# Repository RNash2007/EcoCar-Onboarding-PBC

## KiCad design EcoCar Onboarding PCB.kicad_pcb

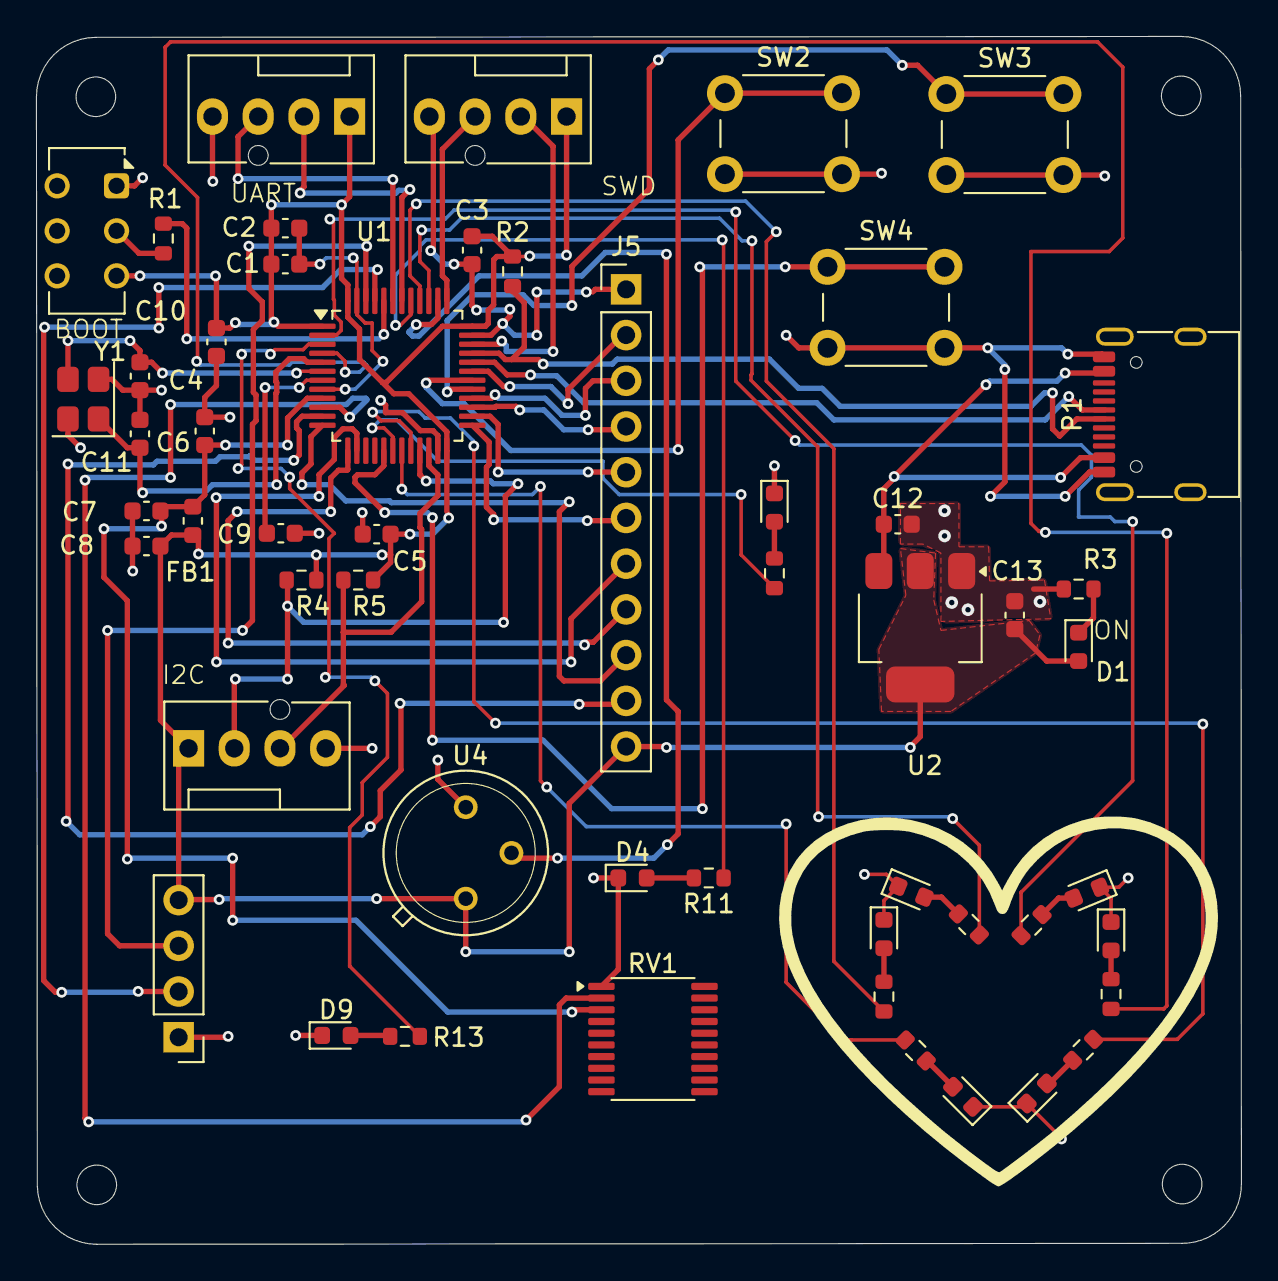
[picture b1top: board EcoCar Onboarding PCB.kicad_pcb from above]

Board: 2 copper layers, 66.9 x 67.1 mm, 57 parts (0 on the bottom side), 52 nets.

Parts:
C1, C2, C3, C4, C9: 100n; C_0603_1608Metric
C5: 10u; C_0603_1608Metric
C6: 10n; C_0603_1608Metric
C7, C8: 1u; C_0603_1608Metric
C10, C11: 10p; C_0603_1608Metric
C12, C13: 22u; C_0603_1608Metric
D1, D9: RED; LED_0603_1608Metric
D2, D3, D5, D6, D8, D10: PINK; LED_0603_1608Metric
D4: GREEN; LED_0603_1608Metric
D7: BLUE; LED_0603_1608Metric
FB1: 120R; L_0603_1608Metric
H1, H2, H3, H4: MountingHole; MountingHole_2.2mm_M2
J1: Conn_01x04_Pin; PinHeader_1x04_P2.54mm_Vertical
J2, J3, J4: Conn_01x04_Pin; FanPinHeader_1x04_P2.54mm_Vertical
J5: Conn_01x11_Pin; PinHeader_1x11_P2.54mm_Vertical
P1: USB_C_Plug_USB2.0; USB_C_Receptacle_G-Switch_GT-USB-7010ASV
R1: 10k; R_0603_1608Metric
R2, R3, R4, R5, R6, R7, R8, R9, R10, R11, R12, R13, R14: 1k5; R_0603_1608Metric
RV1: R_Potentiometer; TSSOP-20_4.4x6.5mm_P0.65mm
SW1: SW_SPDT; SW_CK_JS202011CQN_DPDT_Straight
SW2, SW3, SW4: SW_Push; SW_PUSH_6mm_H5mm
U1: STM32F103C8T6; LQFP-48_7x7mm_P0.5mm
U2: AMS1117-3.3; SOT-223-3_TabPin2
U4: ZRE200GE; TO5
Y1: 16MHz; Crystal_SMD_3225-4Pin_3.2x2.5mm

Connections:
+3.3V: C1.1, C2.1, C3.1, C4.1, C5.1, C8.1, C13.1, D1.2 (A), FB1.1, J1.4, J2.1, J3.1, J4.1, J5.11, R2.1, R4.1, R5.1, SW1.3 (C), U1.1 (VBAT), U1.24 (VDD), U1.36 (VDD), U1.48 (VDD), U2.2 (VO), U4.1
+3.3VA: C6.1, C7.1, FB1.2, RV1.3, U1.9 (VDDA)
/BOOT0: R1.2, U1.44 (BOOT0)
/HSE_IN: C11.1, U1.5 (PD0), Y1.1
/HSE_OUT: C10.1, U1.6 (PD1), Y1.3
/I2C2_SCL: J4.2, R4.2, U1.21 (PB10)
/I2C2_SDA: J4.3, R5.2, U1.22 (PB11)
/LED1: R6.1, U1.19 (PB1)
/LED2: R7.1, U1.20 (PB2)
/LED3: R9.1, U1.39 (PB3)
/LED4: R10.1, U1.40 (PB4)
/LED5: R11.1, U1.41 (PB5)
/LED6: R12.1, U1.4 (PC15)
/LED7: R13.1, U1.3 (PC14)
/LED8: R14.1, U1.2 (PC13)
/NRST: C9.1, U1.7 (NRST)
/P1: J5.2, U1.31 (PA10)
/P2: J5.3, U1.28 (PB15)
/P3: J5.4, U1.27 (PB14)
/P4: J5.5, U1.26 (PB13)
/P5: J5.6, U1.25 (PB12)
/P6: J5.7, U1.14 (PA4)
/P7: J5.8, U1.13 (PA3)
/P8: J5.9, U1.12 (PA2)
/P9: J5.10, U1.11 (PA1)
/PWR_LED_K: D1.1 (K), R3.1
/Pins for screen: J1.3, U1.46 (PB9)
/SWCLK: J2.3, U1.37 (PA14)
/SWDIO: J2.2, U1.34 (PA13)
/SW_BOOT0: R1.1, SW1.2 (B)
/TIMER_LED: R8.1, U1.18 (PB0)
/USART1_RX: J3.3, U1.43 (PB7)
/USART1_TX: J3.2, U1.42 (PB6)
/USB_D+: P1.A6 (D+), R2.2, U1.33 (PA12)
/USB_D-: P1.A7 (D-), U1.32 (PA11)
GND: C1.2, C2.2, C3.2, C4.2, C5.2, C6.2, C7.2, C8.2, C9.2, C10.2, C11.2, C12.2, C13.2, D2.1 (K), D3.1 (K), D4.1 (K), D5.1 (K), D6.1 (K), D7.1 (K), D8.1 (K), D9.1 (K), D10.1 (K), J1.1, J2.4, J3.4, J4.4, J5.1, P1.A1 (GND), P1.A12 (GND), P1.B1 (GND), P1.B12 (GND), R3.2, RV1.1, SW1.1 (A), SW2.2, SW3.2, SW4.2, U1.8 (VSSA), U1.23 (VSS), U1.35 (VSS), U1.47 (VSS), U2.1 (GND), U4.3, Y1.2 (G), Y1.4 (G)
unnamed: D2.2 (A), R10.2
unnamed: D3.2 (A), R6.2
unnamed: D4.2 (A), R11.2
unnamed: D5.2 (A), R12.2
unnamed: D6.2 (A), R7.2
unnamed: D7.2 (A), R8.2
unnamed: D8.2 (A), R9.2
unnamed: D9.2 (A), R13.2
unnamed: D10.2 (A), R14.2
unnamed: J1.2, U1.45 (PB8)
unnamed: RV1.2, U1.10 (PA0)
unnamed: SW4.1, U1.17 (PA7)
unnamed: SW3.1, U1.29 (PA8)
unnamed: SW2.1, U1.30 (PA9)
unnamed: U1.38 (PA15), U4.2
VBUS: C12.1, P1.A4 (VBUS), P1.A9 (VBUS), P1.B4 (VBUS), P1.B9 (VBUS), U2.3 (VI)

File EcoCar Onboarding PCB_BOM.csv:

"Reference","Qty","Value","DNP","Exclude from BOM","Exclude from Board","Exclude from Simulation","Exclude from Position Files","Footprint","Datasheet"
"C1,C2,C3,C4,C9","5","100n","","","","","${EXCLUDE_FROM_POS_FILES}","Capacitor_SMD:C_0603_1608Metric",""
"C5","1","10u","","","","","${EXCLUDE_FROM_POS_FILES}","Capacitor_SMD:C_0603_1608Metric",""
"C6","1","10n","","","","","${EXCLUDE_FROM_POS_FILES}","Capacitor_SMD:C_0603_1608Metric",""
"C7,C8","2","1u","","","","","${EXCLUDE_FROM_POS_FILES}","Capacitor_SMD:C_0603_1608Metric",""
"C10,C11","2","10p","","","","","${EXCLUDE_FROM_POS_FILES}","Capacitor_SMD:C_0603_1608Metric",""
"C12,C13","2","22u","","","","","${EXCLUDE_FROM_POS_FILES}","Capacitor_SMD:C_0603_1608Metric",""
"D1,D9","2","RED","","","","","${EXCLUDE_FROM_POS_FILES}","LED_SMD:LED_0603_1608Metric",""
"D2,D3,D5,D6,D8,D10","6","PINK","","","","","${EXCLUDE_FROM_POS_FILES}","LED_SMD:LED_0603_1608Metric",""
"D4","1","GREEN","","","","","${EXCLUDE_FROM_POS_FILES}","LED_SMD:LED_0603_1608Metric",""
"D7","1","BLUE","","","","","${EXCLUDE_FROM_POS_FILES}","LED_SMD:LED_0603_1608Metric",""
"FB1","1","120R","","","","","${EXCLUDE_FROM_POS_FILES}","Inductor_SMD:L_0603_1608Metric",""
"J1","1","Conn_01x04_Pin","","","","","${EXCLUDE_FROM_POS_FILES}","Connector_PinHeader_2.54mm:PinHeader_1x04_P2.54mm_Vertical",""
"J2,J3,J4","3","Conn_01x04_Pin","","","","","${EXCLUDE_FROM_POS_FILES}","Connector:FanPinHeader_1x04_P2.54mm_Vertical",""
"J5","1","Conn_01x11_Pin","","","","","${EXCLUDE_FROM_POS_FILES}","Connector_PinHeader_2.54mm:PinHeader_1x11_P2.54mm_Vertical",""
"P1","1","USB_C_Plug_USB2.0","","","","","${EXCLUDE_FROM_POS_FILES}","Connector_USB:USB_C_Plug_JAE_DX07P024AJ1","https://www.usb.org/sites/default/files/documents/usb_type-c.zip"
"R1","1","10k","","","","","${EXCLUDE_FROM_POS_FILES}","Resistor_SMD:R_0603_1608Metric",""
"R2,R3,R4,R5,R6,R7,R8,R9,R10,R11,R12,R13,R14","13","1k5","","","","","${EXCLUDE_FROM_POS_FILES}","Resistor_SMD:R_0603_1608Metric",""
"RV1","1","R_Potentiometer","","","","","${EXCLUDE_FROM_POS_FILES}","Package_SO:TSSOP-20_4.4x6.5mm_P0.65mm",""
"SW1","1","SW_SPDT","","","","","${EXCLUDE_FROM_POS_FILES}","Button_Switch_THT:SW_CK_JS202011CQN_DPDT_Straight",""
"SW2,SW3,SW4","3","SW_Push","","","","","${EXCLUDE_FROM_POS_FILES}","Button_Switch_THT:SW_PUSH_6mm_H5mm",""
"U1","1","STM32F103C8T6","","","","","${EXCLUDE_FROM_POS_FILES}","Package_QFP:LQFP-48_7x7mm_P0.5mm","https://www.st.com/resource/en/datasheet/stm32f103c8.pdf"
"U2","1","AMS1117-3.3","","","","","${EXCLUDE_FROM_POS_FILES}","Package_TO_SOT_SMD:SOT-223-3_TabPin2","http://www.advanced-monolithic.com/pdf/ds1117.pdf"
"U4","1","ZRE200GE","","","","","${EXCLUDE_FROM_POS_FILES}","TEST:TO5",""
"Y1","1","16MHz","","","","","${EXCLUDE_FROM_POS_FILES}","Crystal:Crystal_SMD_3225-4Pin_3.2x2.5mm",""
